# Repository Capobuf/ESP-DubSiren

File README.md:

# ESP32-S3 Dub Siren

Dub siren controllata da una GUI Windows. Il DSP gira interamente sull'ESP32-S3
e il PCM mono già elaborato può essere inviato al PC, a un DAC PCM5102A via
I2S, oppure a entrambe le destinazioni senza resampling.

La baseline predefinita **Classic** offre SINE 1, SINE 2, TEST TONE e
SQUARE, Pitch a tre posizioni e Rate a tre velocità più Manual. Il dry usa solo
un gate anti-click di 2 ms in attacco e 3 ms in rilascio. Echo Level zero esclude
completamente il wet. Le voci e la risposta dei controlli hanno una taratura
di progetto; una corrispondenza sonora con strumenti esterni non è misurata.

**Extended** conserva Lickshot, Sonar, Syndrum, Gunshot, Dynamic Sweep, forme
LFO aggiuntive e controlli avanzati, e aggiunge i carrier SAW e TRIANGLE.
Sine 1 e Sine 2 usano le stesse voci di
Classic; Sonar emette ping pulsanti con cadenza regolata da Rate.
Il DSP/control C++ è condiviso da firmware
e Virtual ESP. Tarature, fonti e limiti sono in [controls](docs/controls.md);
le verifiche della revisione sono in [baseline validation](docs/baseline-validation.md).

## Requisiti Windows

- ESP32-S3 DevKitC-1 collegata con un cavo USB dati
- modulo DAC PCM5102A per l'uscita audio GPIO
- display Adafruit 5393 / ST7789 opzionale per lo sviluppo firmware; il
  montaggio sul PCB resta da validare, come descritto sotto
- VS Code con estensione PlatformIO IDE, oppure PlatformIO Core 6.x
- Python 3.11 o successivo (verificato con Python 3.13.14)
- uscita audio Windows

La configurazione usa il profilo PlatformIO `esp32-s3-devkitc-1-n16r8`,
flash da 16 MB, Hardware CDC e USB Serial/JTAG. Il display non richiede PSRAM.

## Preparazione

Aprire un prompt nella cartella `pc` ed eseguire una volta:

```bat
setup.bat
```

Lo script crea `.venv`, aggiorna pip e installa `pyserial`, `sounddevice`
e il compilatore host `ziglang` per Virtual ESP.

## Build e upload firmware

Da un terminale nella cartella `firmware`:

```powershell
python -m platformio run
python -m platformio run --target upload --upload-port COM6
```

Sostituire `COM6` con la porta effettiva. Usare la connessione USB nativa che
Windows identifica come Espressif USB Serial/JTAG (`VID 303A`, `PID 1001`), non
una porta Bluetooth. Al primo upload può essere necessario entrare nel
bootloader: tenere premuto **BOOT**, premere e rilasciare **RESET/EN**, quindi
rilasciare **BOOT**. Dopo l'upload, se resta nel bootloader, premere una volta
solo **RESET/EN**.

In VS Code sono equivalenti i comandi **PlatformIO: Build** e
**PlatformIO: Upload**.

## Collegamento PCM5102A

Il DAC usa I2S Philips standard a 48 kHz, stereo 16 bit. Il firmware duplica
ogni campione mono sui canali sinistro e destro; il PCM5102A ricava internamente
il clock necessario e non richiede MCLK dall'ESP32.

```text
ESP32 GPIO16 -> PCM5102A BCK
ESP32 GPIO17 -> PCM5102A LCK
ESP32 GPIO18 -> PCM5102A DIN
PCM5102A SCL/SCK -> GND
PCM5102A FMT -> GND
```

## Avvio

Dalla cartella `pc`:

```bat
run.bat
```

La GUI funziona sia con l'ESP32-S3 reale sia senza hardware tramite **Virtual ESP**.
Il Virtual ESP compila e usa direttamente gli stessi sorgenti C++ DSP/control
del firmware; la libreria host viene ricompilata automaticamente quando quei
sorgenti cambiano.

La superficie predefinita presenta PITCH, RATE, ECHO LEVEL, ECHO TIME,
ECHO FEEDBACK ed ECHO FILTER; BTN1 TRIGGER, BTN2 HOLD, BTN3 MANUAL MOD e
BTN4 ECHO CUT. L'encoder cicla i quattro voicing; premendolo si apre il menu
al rilascio del click. I sei pot e i quattro pulsanti sono configurabili per
profilo dal controller C++ condiviso; Pickup evita salti dopo cambio profilo o
parametro. In Extended la rotazione libera cambia la variante del pad;
BTN1 premuto + rotazione regola Depth. Con gli altri pulsanti sonori
fisicamente premuti, l'encoder applica un transpose live temporaneo; in
Classic vale anche per BTN1. Il Master resta separato e non assegnabile sul
retro. La Home 320x172 mostra insieme etichette e valori fisici, con overlay
temporanei dei pot.
Il prodotto finale userà un display piccolo, principalmente testuale, per
stato, parametri, menu e impostazioni. Classic ed Extended mostrano solo testo;
il driver ST7789 usa la configurazione del 5393, ancora da verificare su hardware.
Dettagli: [pannello UI](docs/panel-ui.md).

Per lavorare senza hardware:

1. scegliere **Virtual ESP** nel selettore Device;
2. premere **Connect**;
3. premere **Start Audio**;
4. usare normalmente tutti i controlli della sirena.

In modalità Virtual ESP l'uscita è sempre **PC**. La catena fisica
I2S -> PCM5102A -> uscita analogica non è emulata.

Con l'hardware reale:

1. premere **Refresh** e scegliere la COM Espressif;
2. scegliere **PC**, **PCM5102A** o **Both** nel selettore Output;
3. premere **Connect** e attendere `Connected · firmware 0.9.0`;
4. premere **Start Audio**;
5. usare BTN1 Trigger, BTN2 Hold, BTN3 Manual Mod e BTN4 Echo Cut;
   ruotare l'encoder per scegliere il voicing, premerlo per il menu.

**Stop Audio** silenzia sia il PC sia il DAC. **Connect** prende il controllo
delle uscite e le mantiene silenziose fino a **Start Audio**; **Disconnect**
le silenzia e chiude audio, thread e seriale. Il DSP continua a elaborare le
code echo. Dopo Disconnect il DAC resta disabilitato fino a un nuovo Start,
`LOCAL_AUDIO 1` o riavvio; all'accensione l'uso autonomo resta abilitato.
Per un controllo automatico dell'hardware collegato:

```powershell
.venv\Scripts\python.exe smoke_test.py COM6
```

Dettagli: [architettura](docs/architecture.md), [protocollo](docs/protocol.md) e
[controlli](docs/controls.md).

Per creare ventotto brevi WAV di confronto direttamente dal PCM firmware
(con la scheda collegata), eseguire dalla cartella `pc`:

```powershell
.venv\Scripts\python.exe performance_capture.py COM6
```

Lo script stampa la directory temporanea che contiene i WAV. Usare
`--output-dir <percorso>` per scegliere una destinazione persistente. Il profilo
CLASSIC offre preset di progetto, non una riproduzione misurata di altri modelli.
Le capture includono Dynamic Sweep su SINE1/LICKSHOT/SONAR, Syndrum up/down e
sine/square, più Gunshot dry/echo; richiedono hardware reale e non costituiscono
uno smoke test I2S/DAC.

## Test

La [CI](.github/workflows/ci.yml) esegue i test Python/Virtual ESP e DSP nativi
su Windows e compila entrambi i firmware su Ubuntu. I binari e i file ELF
sono pubblicati come artefatti del run, separati per ambiente. Non viene
eseguito alcun upload su scheda. Le versioni firmware sono fissate in
`firmware/platformio.ini`; la CI usa PlatformIO 6.2.0.

```powershell
pc\.venv\Scripts\python.exe -m unittest discover -s pc -p "test_*.py" -f
pc\.venv\Scripts\python.exe tests\native\run.py
pc\.venv\Scripts\python.exe -m platformio run -d firmware -e esp32-s3-devkitc-1-n16r8 -e panel-prototype
```

Il test nativo usa Zig C++ (`pip install ziglang`) oppure il compilatore indicato
da `CXX`; esegue parser e DSP senza scheda. Con hardware collegato, leggere
`renderUs`, `maxRenderUs`, `cycleUs` e `maxCycleUs` da STATUS durante gli scenari
di sweep e verificare che restino sotto 10.000 µs per blocco.
`displayRenderUs` e `maxDisplayRenderUs` misurano separatamente il ridisegno
del testo ST7789 e devono restare sotto il budget display di 100.000 µs.

## Hardware

**PCB desktop a vista** 86 × 126 mm, senza custodia obbligatoria:
ESP32-S3-WROOM-1U, DAC Adafruit 6250 e display Adafruit 5393, solder mask nero
con finitura ENIG, quattro fissaggi M3. Il PCB è instradato e passa il DRC; il
montaggio fisico resta da provare sul prototipo.

- [Hardware: stato, decisioni e file](hardware/README.md)
- [Riferimento tecnico del PCB](hardware/docs/pcb.md), [guida di montaggio DIY](hardware/docs/assembly.md)

Il firmware configura il 5393 con `init(172, 320)` e rotazione landscape,
ottenendo un'area runtime di 320×172. Usa lo SPI hardware esistente:

```text
GPIO7  -> TFT RST
GPIO8  -> TFT DC
GPIO9  -> TFT CS
GPIO11 -> TFT MOSI
GPIO12 -> TFT SCK
GPIO14 -> backlight (livello fisso HIGH)
```

GPIO13/MISO non serve al TFT write-only e la microSD del breakout non è
implementata. Le librerie sono **Adafruit GFX Library** e **Adafruit ST7735 and
ST7789 Library**. In base alla [guida ufficiale Adafruit 5393](https://learn.adafruit.com/adafruit-1-47-round-rectangle-tft-display/arduino-wiring-test),
gli offset del pannello sono gestiti dalla libreria.

Il funzionamento del display sull'hardware reale e l'integrazione del firmware
con la scheda definitiva restano da verificare.

## Firmware per il pannello autonomo (issue #5-#12)

La revisione aggiunge articolazioni Lickshot, Tone/Contour, Echo Color,
menu Sound/Mod/Echo/Setup e quattro memorie Extended con SAVE/RECALL.
Vedi [controlli](docs/controls.md), [menu e memorie](docs/panel-ui.md) e
[pinout, build autonoma e verifiche hardware pendenti](docs/standalone.md).
`STREAM 0` interrompe soltanto USB; `LOCAL_AUDIO 0` silenzia l'uscita locale.
Le nuove tarature sonore richiedono ascolto e misure sull'ESP.

Il [tap tempo](docs/tempo.md) aggiunge BPM e divisioni ritmiche indipendenti
per Echo e LFO, con azione pulsante assegnabile e accesso dal menu.

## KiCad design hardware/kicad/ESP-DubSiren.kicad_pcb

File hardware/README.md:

# ESP-DubSiren — hardware

PCB desktop a vista, unico progetto KiCad attivo. Instradato, con DRC a 0 errori
(18 esclusioni volute per lo stack U5/U6), 0 connessioni aperte e schema allineato.
Gerber e forature per JLCPCB generati l'8/11/2026 in [fab/](fab/), non ancora ordinati.

## File

| Cosa | Dove |
|---|---|
| Progetto, schema, PCB | [kicad/ESP-DubSiren.kicad_pro](kicad/ESP-DubSiren.kicad_pro), [schema](kicad/ESP-DubSiren.kicad_sch), [PCB](kicad/ESP-DubSiren.kicad_pcb) |
| Librerie locali | [footprint](kicad/footprints/), [simboli](kicad/symbols/) |
| Riferimento tecnico del PCB | [docs/pcb.md](docs/pcb.md) |
| Gerber e forature JLCPCB | [fab/ESP-DubSiren-JLCPCB-2026-11-08.zip](fab/ESP-DubSiren-JLCPCB-2026-11-08.zip), file singoli e mappe fori in [fab/ESP-DubSiren-JLCPCB-2026-11-08/](fab/ESP-DubSiren-JLCPCB-2026-11-08/) |
| Montaggio DIY | [docs/assembly.md](docs/assembly.md) |
| Distinta e acquisti | [docs/BOM.csv](docs/BOM.csv), [docs/acquisti.csv](docs/acquisti.csv) |
| Datasheet e disegni | [docs/sources.md](docs/sources.md), [cad/sources/](cad/sources/) |
| Modelli 3D | [cad/3dmodels/](cad/3dmodels/README.md), generati e assegnati con [tools/](tools/) |

## Decisioni in vigore

- **Scheda:** 86 × 126 mm, angoli R3, 2 strati, 1,6 mm. Nessuna custodia, staffa
  USB o stampa 3D obbligatoria; si usa orizzontale o leggermente inclinata.
- **Produzione:** JLCPCB, solder mask nero, finitura ENIG 1µ", serigrafia bianca.
  Sono già impostati nello stackup del PCB; vanno selezionati anche nell'ordine.
- **Fissaggi:** quattro fori M3 Ø3,2 NPTH in (5;−1), (81;−1), (5;115), (81;115),
  interassi 76 × 116 mm, con riserve 8 × 8 mm senza rame su entrambe le facce.
  Origine KiCad: bordo posteriore Y=−6, anteriore Y=120.
- **Fronte (F.Cu):** RV1–3 in alto, display U5 (Adafruit 5393) al centro con
  encoder SW7 a destra, RV4–6 sotto, quattro CHERRY SW1–4 in basso.
- **Bordo posteriore:** USB-C J1 (GCT USB4085), jack mono J2 (Neutrik NRJ4HF),
  MASTER RV7. RESET SW5 e BOOT SW6 sul bordo destro.
- **Retro (B.Cu):** tutti gli SMD; ESP32-S3-WROOM-1U-N16R8 (U1) a sinistra.
  Il DAC U6 (Adafruit 6250, senza jack 3,5 mm) sta dietro il display U5:
  header U5 da 2,50 mm, pin U6 tagliati a filo prima di montare U5. Eventuali
  adattamenti (pin più alti o simili) si fanno a mano in montaggio.
- **Uscita audio J2:** T → AUDIO_MONO (OUTL di U6), S → GND, TN/SN non collegati;
  OUTR di U6 non collegato. Il dado NRJ-NUT-B serve solo con un pannello.
- **Archivio Hammond:** lo studio della issue
  [#14](https://github.com/Capobuf/ESP-DubSiren/issues/14) è conservato nel branch
  `codex/issue-14-jack-fit`. Non va eliminato e non vincola il layout.

## Da verificare sul prototipo

- Stack U5/U6: altezza reale fra display e DAC.
- Fit di manopole, keycap e distanziali; stabilità degli appoggi.
- Ripple delle alimentazioni, rumore audio, I²S e display sull'hardware reale.

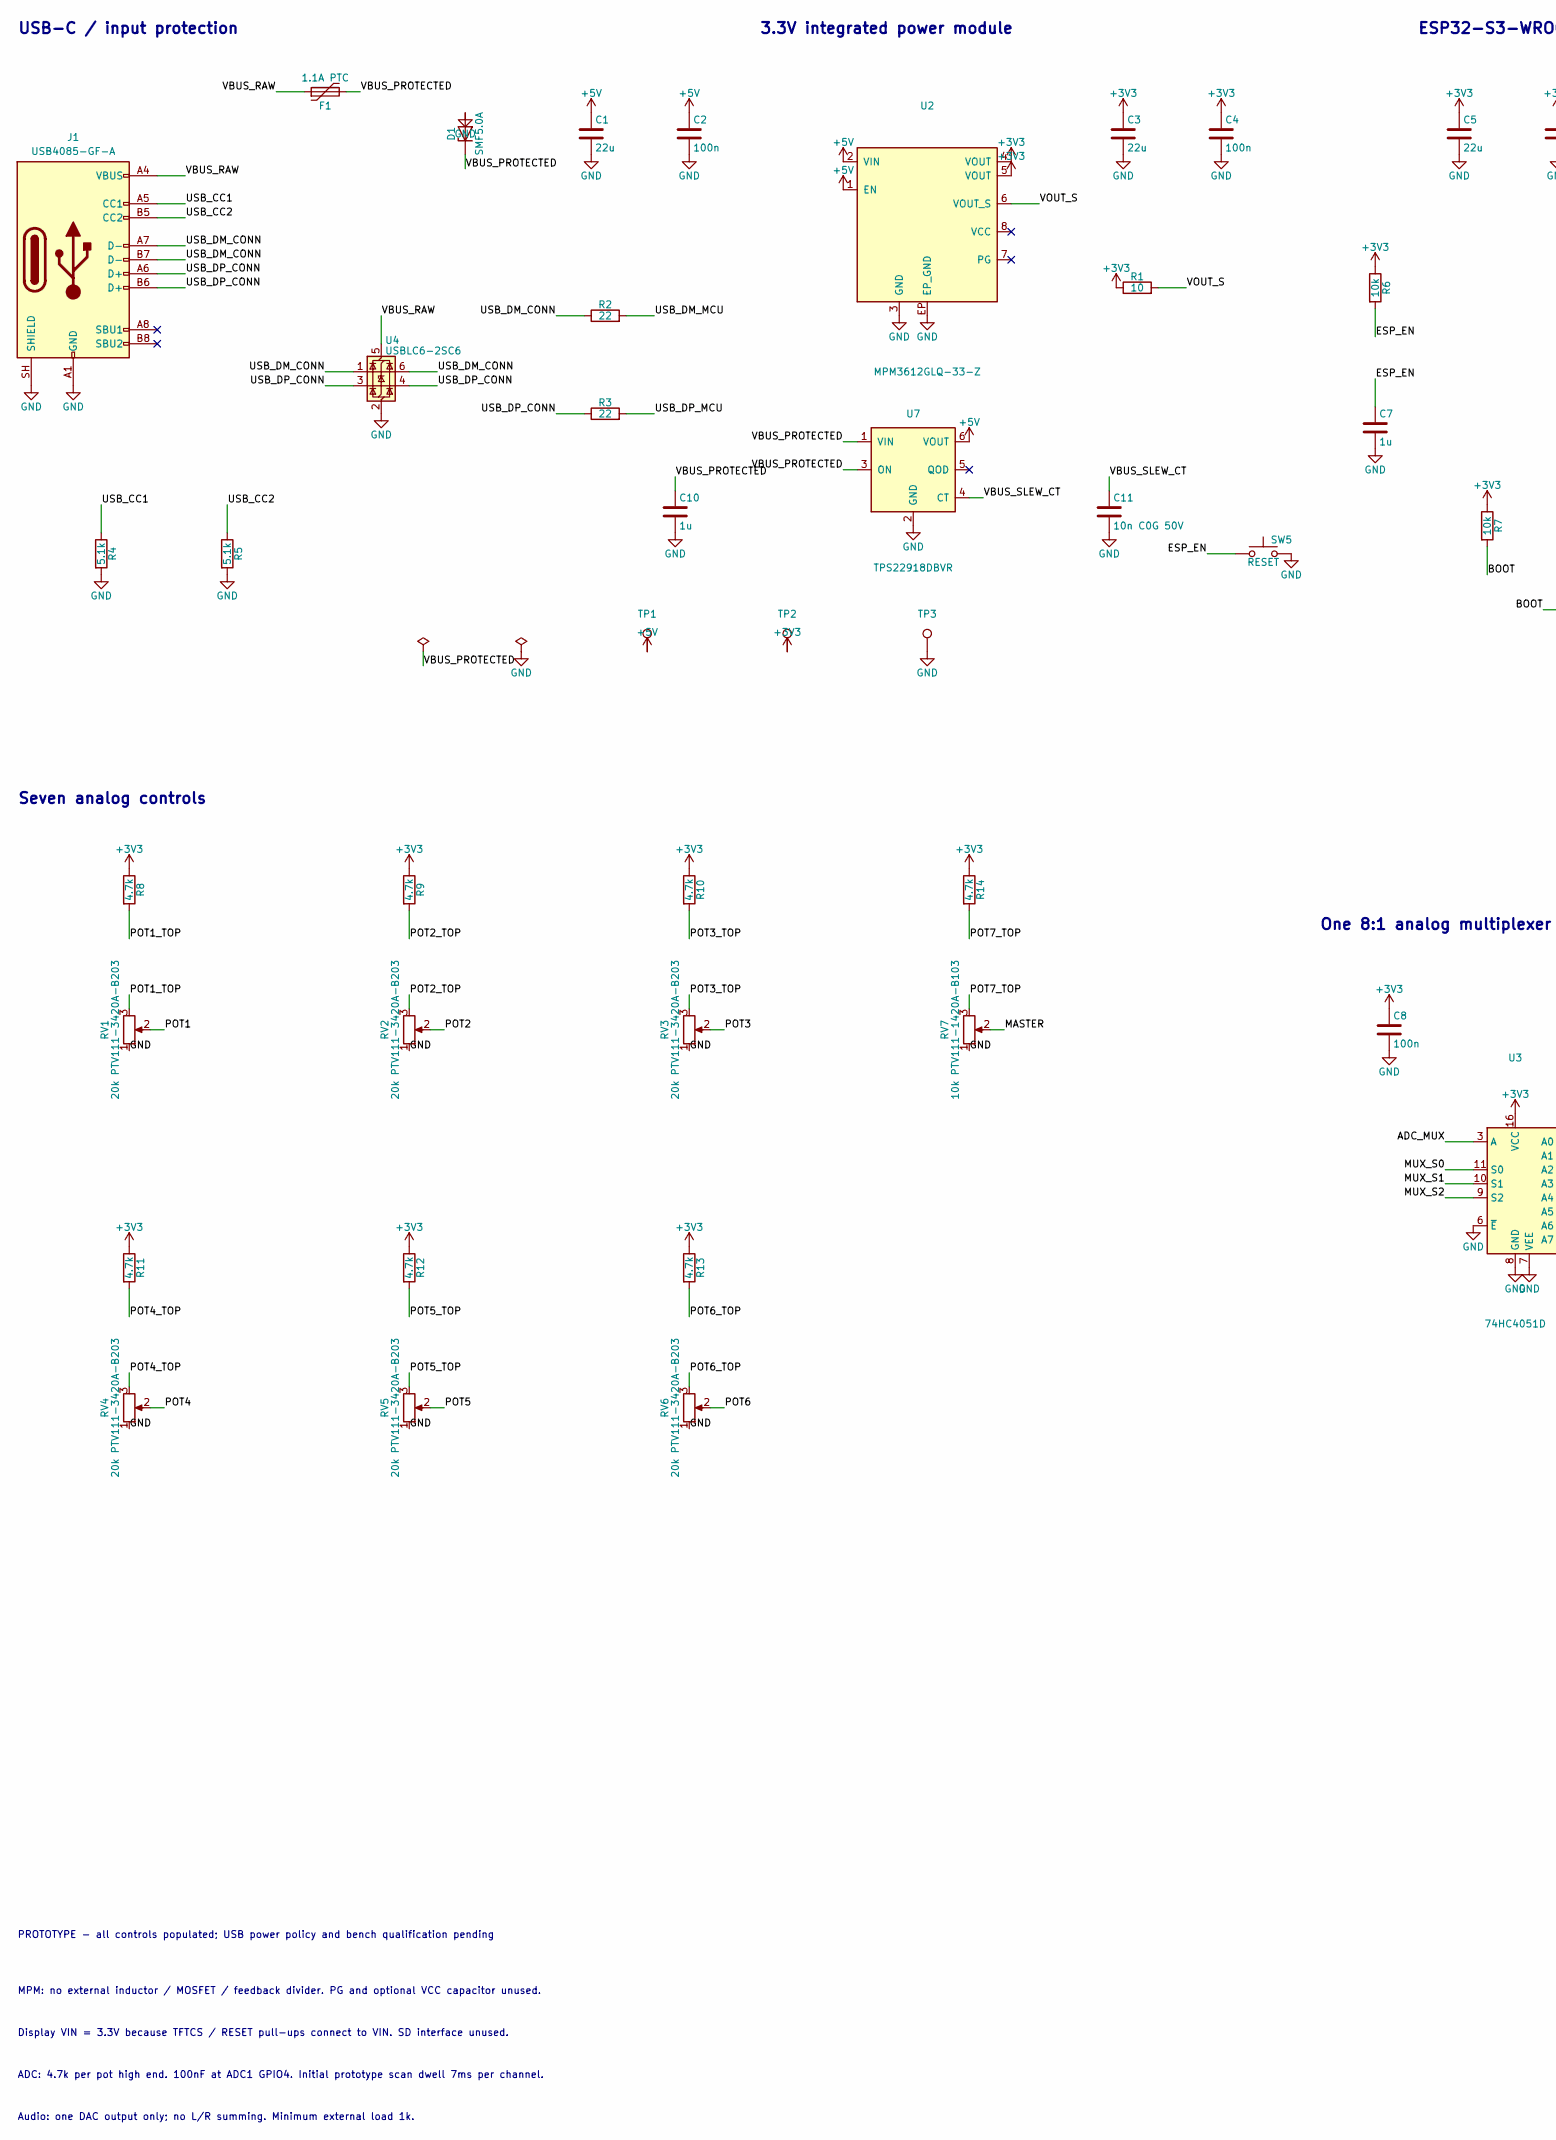
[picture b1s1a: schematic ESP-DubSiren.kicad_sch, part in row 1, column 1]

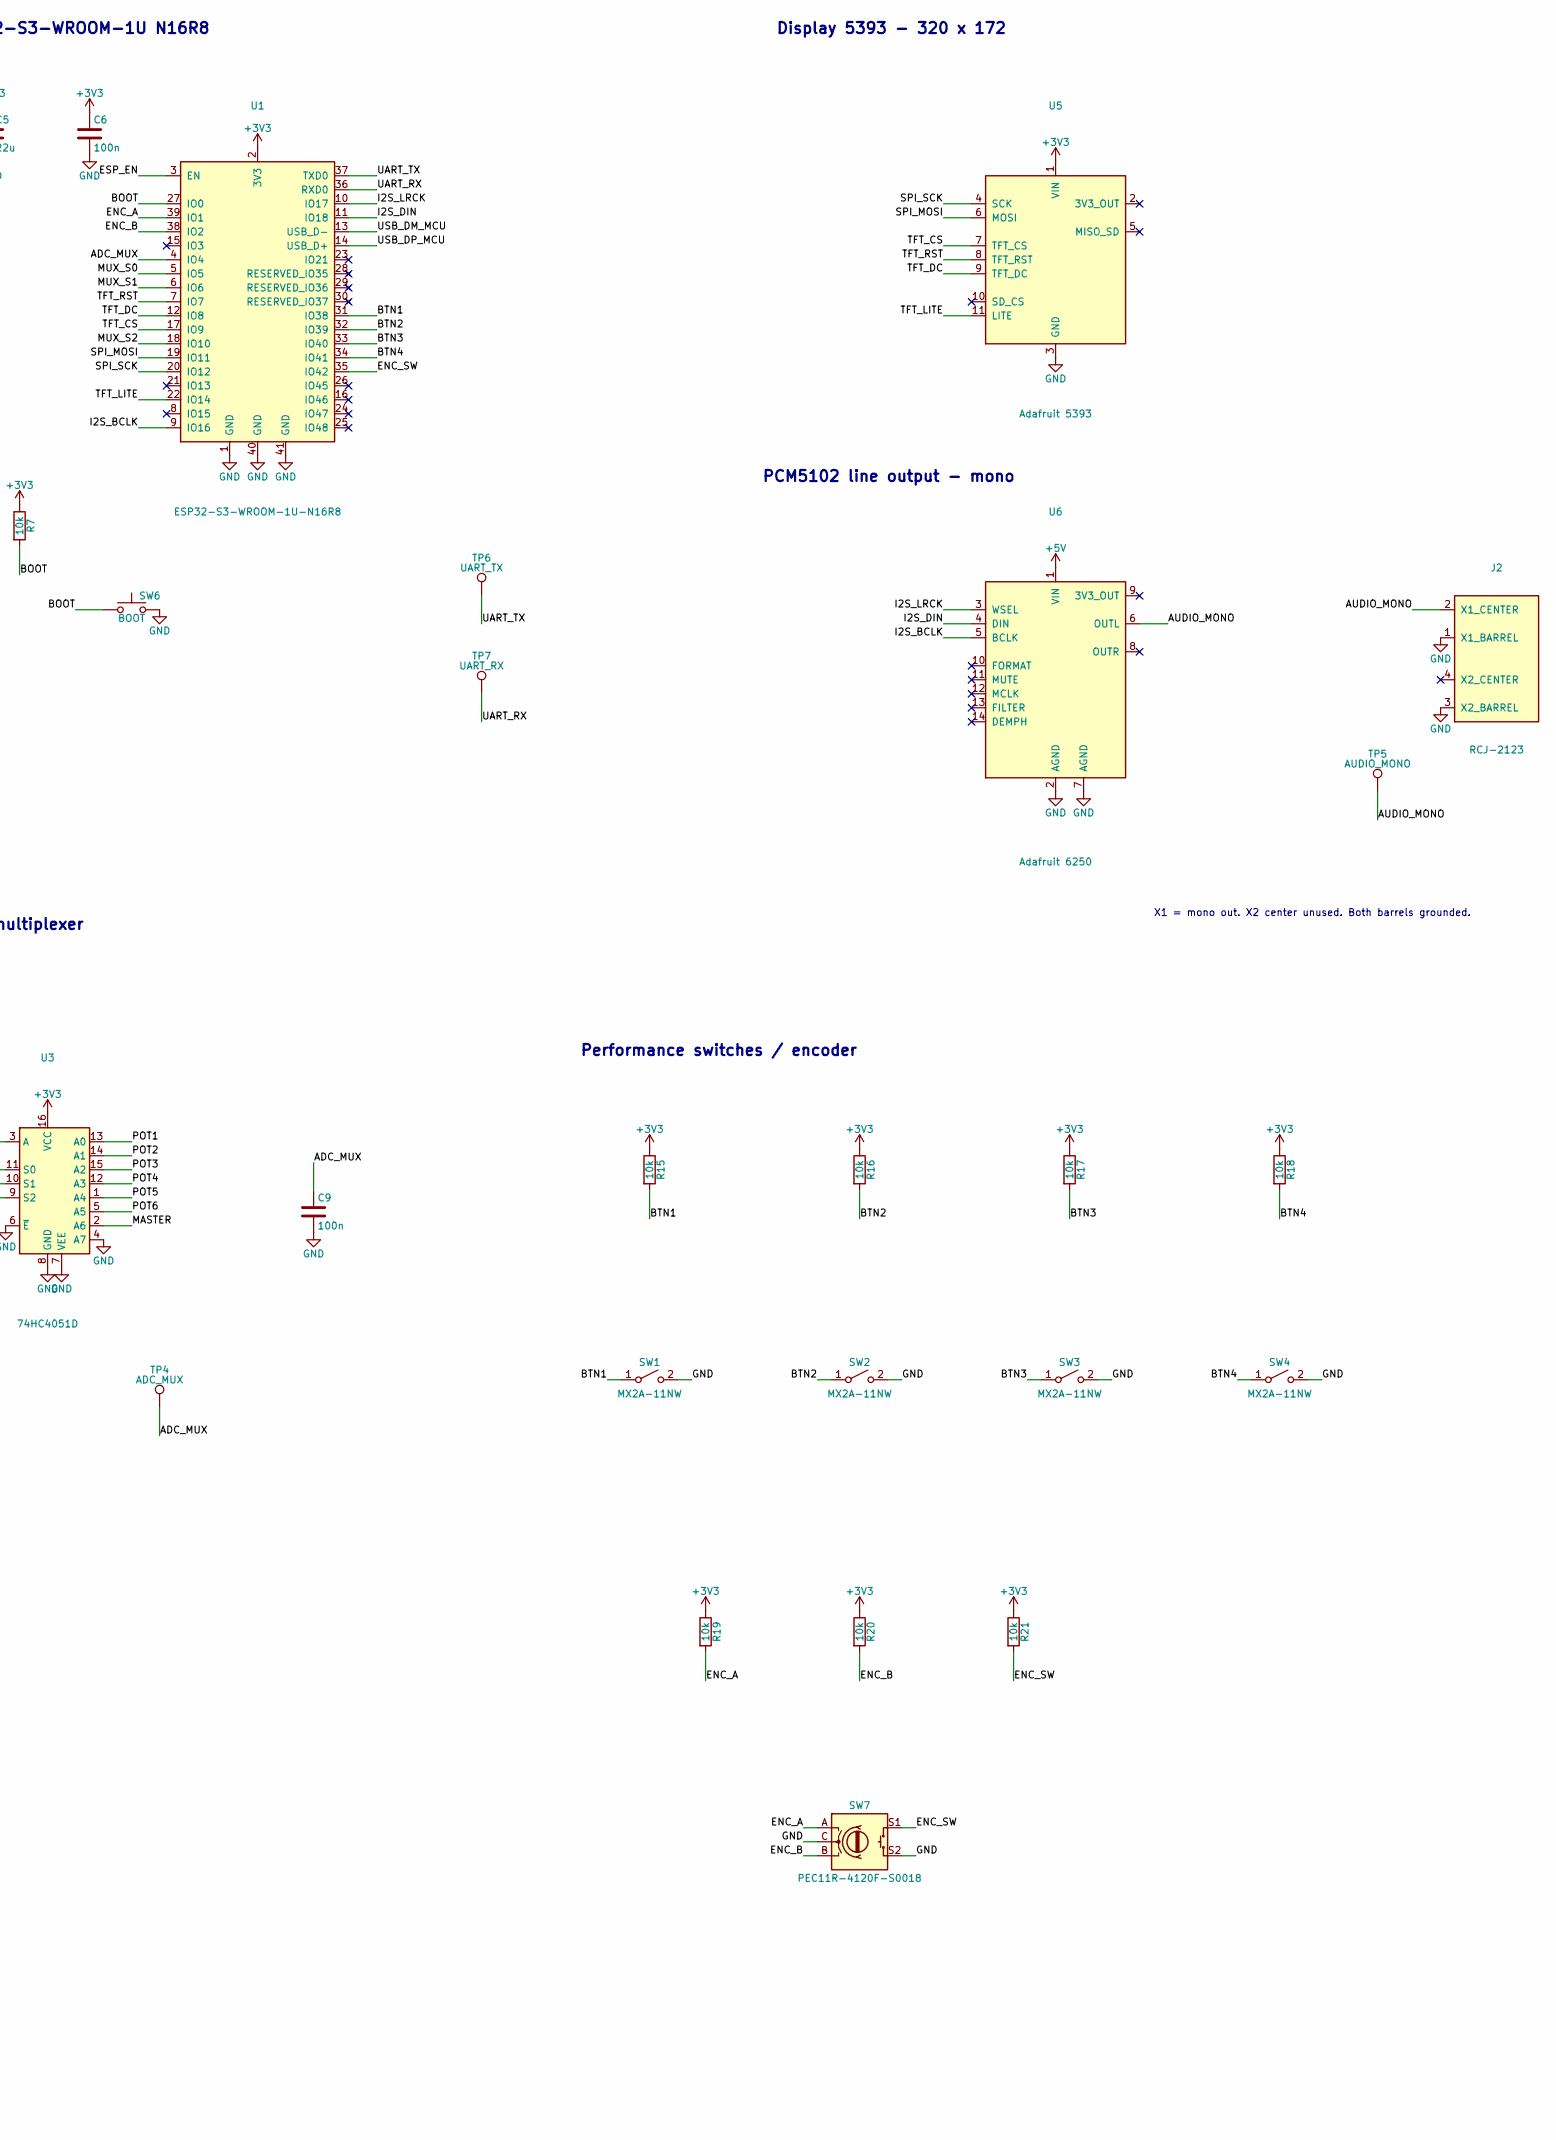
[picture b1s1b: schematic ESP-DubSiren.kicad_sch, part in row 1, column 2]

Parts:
C1, C3, C5: 22u; C_0805_2012Metric; MPN CL21A226MPCLRNC
C2, C4, C6, C8, C9: 100n; C_0603_1608Metric; MPN CL10B104KO8NNNC
C7, C10: 1u; C_0603_1608Metric; MPN CL10B105MO8NNWC
C11: 10n C0G 50V; C_0603_1608Metric; MPN GRM1885C1H103JA01D
D1: SMF5.0A; D_SOD-123F; MPN SMF5.0A_R1_00001
F1: 1.1A PTC; Bel_0ZCG0110CF2B_1812; MPN 0ZCG0110CF2B
J1: USB4085-GF-A; USB_C_Receptacle_GCT_USB4085; MPN USB4085-GF-A
J2: RCJ-2123; SameSky_RCJ-2123; MPN RCJ-2123
R1: 10; R_0603_1608Metric; MPN NRC06J100TRF
R2, R3: 22; R_0603_1608Metric; MPN RC0603JR-0722RL
R4, R5: 5.1k; R_0603_1608Metric; MPN AC0603FR-075K1L
R6, R7, R15, R16, R17, R18, R19, R20, R21: 10k; R_0603_1608Metric; MPN RC0603JR-0710KL
R8, R9, R10, R11, R12, R13, R14: 4.7k; R_0603_1608Metric; MPN RC0603FR-074K7L
RV1, RV2, RV3, RV4, RV5, RV6: 20k PTV111-3420A-B203; Bourns_PTV111-3; MPN PTV111-3420A-B203
RV7: 10k PTV111-1420A-B103; Bourns_PTV111-1; MPN PTV111-1420A-B103
SW1, SW2, SW3, SW4: MX2A-11NW; SW_Cherry_MX_1.00u_PCB; MPN MX2A-11NW
SW5: RESET; CK_PTS636SM43SMTR_LFS; MPN PTS636SM43SMTR LFS
SW6: BOOT; CK_PTS636SM43SMTR_LFS; MPN PTS636SM43SMTR LFS
SW7: PEC11R-4120F-S0018; Bourns_PEC11R-4120F-S0018; MPN PEC11R-4120F-S0018
TP1: +5V; TestPoint_Pad_D1.0mm; MPN PCB test pad
TP2: +3V3; TestPoint_Pad_D1.0mm; MPN PCB test pad
TP3: GND; TestPoint_Pad_D1.0mm; MPN PCB test pad
TP4: ADC_MUX; TestPoint_Pad_D1.0mm; MPN PCB test pad
TP5: AUDIO_MONO; TestPoint_Pad_D1.0mm; MPN PCB test pad
TP6: UART_TX; TestPoint_Pad_D1.0mm; MPN PCB test pad
TP7: UART_RX; TestPoint_Pad_D1.0mm; MPN PCB test pad
U1: ESP32-S3-WROOM-1U-N16R8; Espressif_ESP32-S3-WROOM-1U; MPN ESP32-S3-WROOM-1U-N16R8
U2: MPM3612GLQ-33-Z; MPS_MPM3612GLQ-33_LGA-8-1EP_3x3mm; MPN MPM3612GLQ-33-Z
U3: 74HC4051D; SOIC-16_3.9x9.9mm_P1.27mm; MPN 74HC4051D
U4: USBLC6-2SC6; SOT-23-6; MPN USBLC6-2SC6
U5: Adafruit 5393; Adafruit_5393_DisplayFace; MPN 5393
U6: Adafruit 6250; Adafruit_6250_ComponentFace; MPN 6250
U7: TPS22918DBVR; SOT-23-6; MPN TPS22918DBVR

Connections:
+3V3: C3.1, C4.1, C5.1, C6.1, C8.1, R1.1, R6.1, R7.1, R8.1, R9.1, R10.1, R11.1, R12.1, R13.1, R14.1, R15.1, R16.1, R17.1, R18.1, R19.1, R20.1, R21.1, TP2.1 (1_1), U1.2 (3V3), U2.4 (VOUT), U2.5 (VOUT), U3.16 (VCC), U5.1 (VIN)
+5V: C1.1, C2.1, TP1.1 (1_1), U2.1 (EN), U2.2 (VIN), U6.1 (VIN), U7.6 (VOUT)
/ADC_MUX: C9.1, TP4.1 (1_1), U1.4 (IO4), U3.3 (A)
/AUDIO_MONO: J2.2 (X1_CENTER), J2.T, TP5.1 (1_1), U6.6 (OUTL)
/BOOT: R7.2, SW6.1, U1.27 (IO0)
/BTN1: R15.2, SW1.1 (A), U1.31 (IO38)
/BTN2: R16.2, SW2.1 (A), U1.32 (IO39)
/BTN3: R17.2, SW3.1 (A), U1.33 (IO40)
/BTN4: R18.2, SW4.1 (A), U1.34 (IO41)
/ENC_A: R19.2, SW7.A, U1.39 (IO1)
/ENC_B: R20.2, SW7.B, U1.38 (IO2)
/ENC_SW: R21.2, SW7.S1, U1.35 (IO42)
/ESP_EN: C7.1, R6.2, SW5.1, U1.3 (EN)
/I2S_BCLK: U1.9 (IO16), U6.5 (BCLK)
/I2S_DIN: U1.11 (IO18), U6.4 (DIN)
/I2S_LRCK: U1.10 (IO17), U6.3 (WSEL)
/MASTER: RV7.2, U3.2 (A6)
/MUX_S0: U1.5 (IO5), U3.11 (S0)
/MUX_S1: U1.6 (IO6), U3.10 (S1)
/MUX_S2: U1.18 (IO10), U3.9 (S2)
/POT1: RV1.2, U3.13 (A0)
/POT1_TOP: R8.2, RV1.3
/POT2: RV2.2, U3.14 (A1)
/POT2_TOP: R9.2, RV2.3
/POT3: RV3.2, U3.15 (A2)
/POT3_TOP: R10.2, RV3.3
/POT4: RV4.2, U3.12 (A3)
/POT4_TOP: R11.2, RV4.3
/POT5: RV5.2, U3.1 (A4)
/POT5_TOP: R12.2, RV5.3
/POT6: RV6.2, U3.5 (A5)
/POT6_TOP: R13.2, RV6.3
/POT7_TOP: R14.2, RV7.3
/SPI_MOSI: U1.19 (IO11), U5.6 (MOSI)
/SPI_SCK: U1.20 (IO12), U5.4 (SCK)
/TFT_CS: U1.17 (IO9), U5.7 (TFT_CS)
/TFT_DC: U1.12 (IO8), U5.9 (TFT_DC)
/TFT_LITE: U1.22 (IO14), U5.11 (LITE)
/TFT_RST: U1.7 (IO7), U5.8 (TFT_RST)
/UART_RX: TP7.1 (1_1), U1.36 (RXD0)
/UART_TX: TP6.1 (1_1), U1.37 (TXD0)
/USB_CC1: J1.A5 (CC1), R4.1
/USB_CC2: J1.B5 (CC2), R5.1
/USB_DM_CONN: J1.A7 (D-), J1.B7 (D-), R2.1, U4.1 (I/O1), U4.6 (I/O1)
/USB_DM_MCU: R2.2, U1.13 (USB_D-)
/USB_DP_CONN: J1.A6 (D+), J1.B6 (D+), R3.1, U4.3 (I/O2), U4.4 (I/O2)
/USB_DP_MCU: R3.2, U1.14 (USB_D+)
/VBUS_PROTECTED: C10.1, D1.1 (K), F1.2, U7.1 (VIN), U7.3 (ON)
/VBUS_RAW: F1.1, J1.A4 (VBUS), J1.A9 (VBUS), J1.B4 (VBUS), J1.B9 (VBUS), U4.5 (VBUS)
/VBUS_SLEW_CT: C11.1, U7.4 (CT)
/VOUT_S: R1.2, U2.6 (VOUT_S)
GND: C1.2, C2.2, C3.2, C4.2, C5.2, C6.2, C7.2, C8.2, C9.2, C10.2, C11.2, D1.2 (A), J1.A1 (GND), J1.A12 (GND), J1.B1 (GND), J1.B12 (GND), J1.SH (SHIELD), J2.1 (X1_BARREL), J2.3 (X2_BARREL), J2.S, R4.2, R5.2, RV1.1, RV2.1, RV3.1, RV4.1, RV5.1, RV6.1, RV7.1, SW1.2 (B), SW2.2 (B), SW3.2 (B), SW4.2 (B), SW5.2, SW6.2, SW7.C, SW7.S2, TP3.1 (1_1), U1.1 (GND), U1.40 (GND), U1.41 (GND), U2.3 (GND), U2.EP (EP_GND), U3.4 (A7), U3.6 (~E), U3.7 (VEE), U3.8 (GND), U4.2 (GND), U5.3 (GND), U6.2 (AGND), U6.7 (AGND), U7.2 (GND)

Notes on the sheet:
USB-C / input protection
3.3V integrated power module
ESP32-S3-WROOM-1U N16R8
Display 5393 - 320 x 172
PCM5102 line output - mono
Seven analog controls
One 8:1 analog multiplexer
Performance switches / encoder
MPM: no external inductor / MOSFET / feedback divider. PG and optional VCC capacitor unused.
Display VIN = 3.3V because TFTCS / RESET pull-ups connect to VIN. SD interface unused.
ADC: 4.7k per pot high end. 100nF at ADC1 GPIO4. Initial prototype scan dwell 7ms per channel.
Audio: one DAC output only; no L/R summing. Minimum external load 1k.
X1 = mono out. X2 center unused. Both barrels grounded.
PROTOTYPE - all controls populated; USB power policy and bench qualification pending

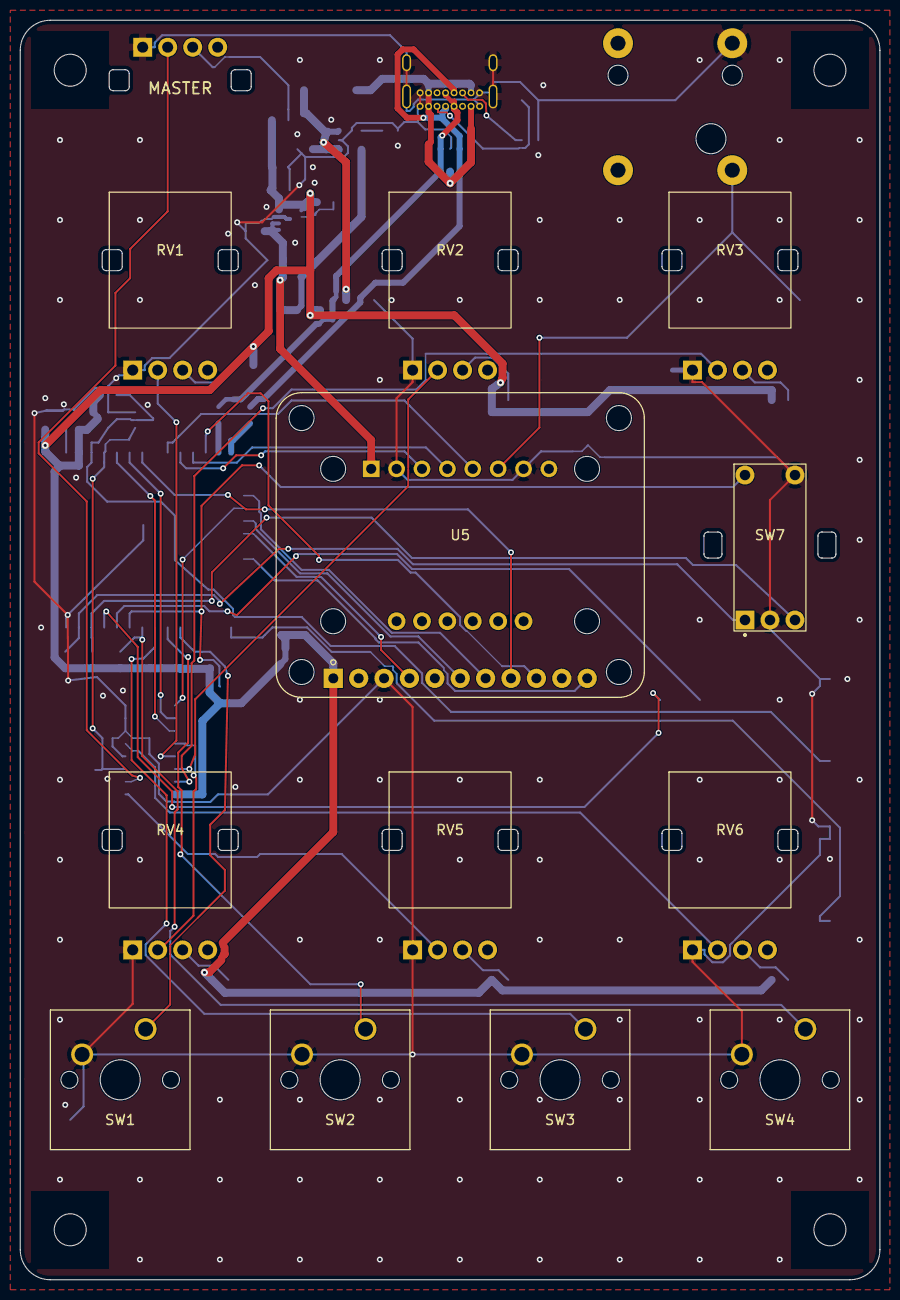
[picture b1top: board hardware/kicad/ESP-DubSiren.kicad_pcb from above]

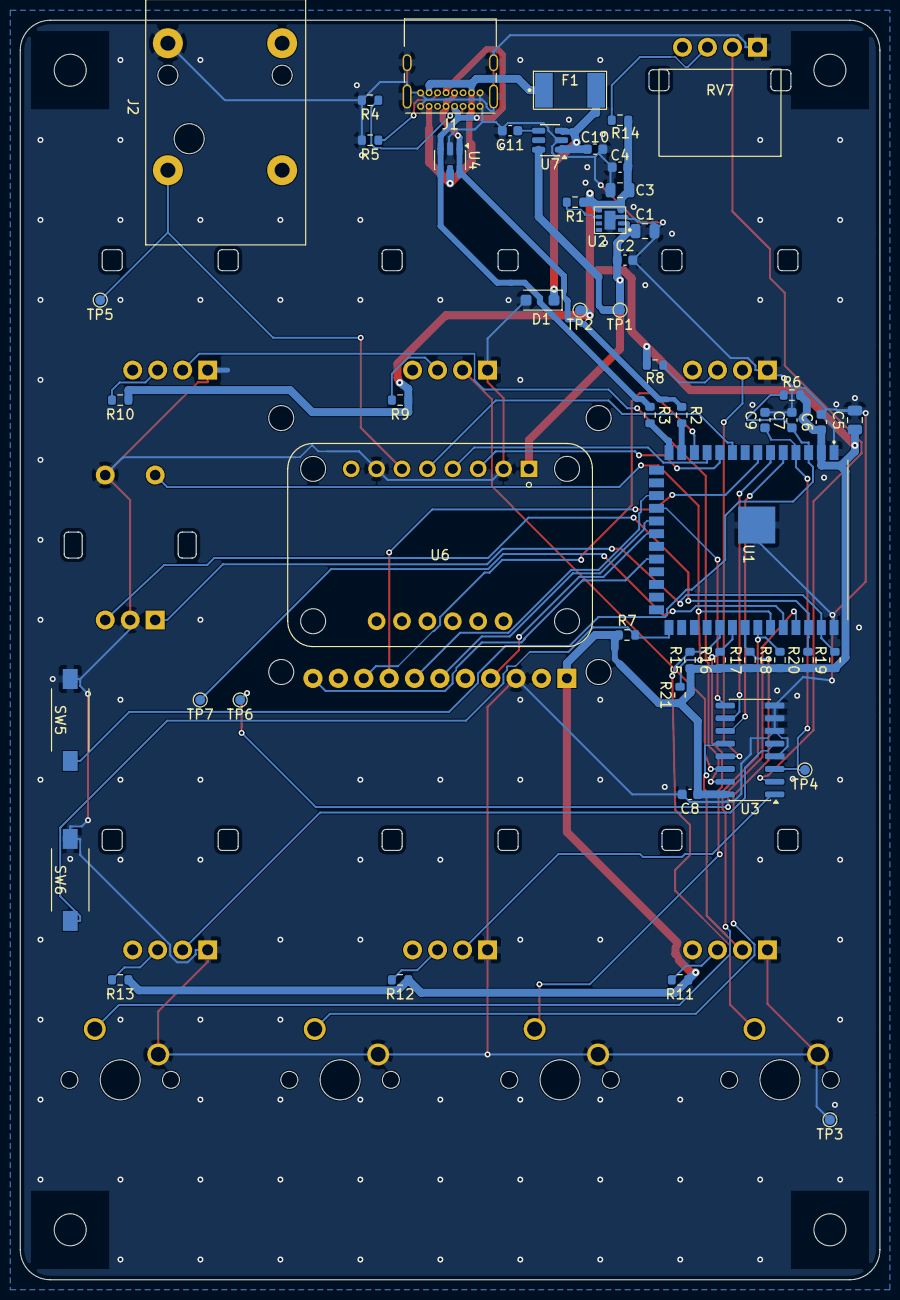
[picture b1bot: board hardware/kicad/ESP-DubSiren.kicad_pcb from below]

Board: 2 copper layers, 86.0 x 126.0 mm, 68 parts (52 on the bottom side), 52 nets.

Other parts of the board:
H1, H2, H3, H4: MountingHole_3.2mm_M3

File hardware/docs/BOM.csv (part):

Reference,Value,Quantity,Footprint,MPN,Manufacturer,Datasheet,DNP,Purchasable,Notes
C1,22u,1,Capacitor_SMD:C_0805_2012Metric,CL21A226MPCLRNC,Samsung,,,yes,Componente dello schema provvisorio; validazione hardware pendente
C2,100n,1,Capacitor_SMD:C_0603_1608Metric,CL10B104KO8NNNC,Samsung,,,yes,Componente dello schema provvisorio; validazione hardware pendente
C3,22u,1,Capacitor_SMD:C_0805_2012Metric,CL21A226MPCLRNC,Samsung,,,yes,Componente dello schema provvisorio; validazione hardware pendente
C4,100n,1,Capacitor_SMD:C_0603_1608Metric,CL10B104KO8NNNC,Samsung,,,yes,Componente dello schema provvisorio; validazione hardware pendente
C5,22u,1,Capacitor_SMD:C_0805_2012Metric,CL21A226MPCLRNC,Samsung,,,yes,Componente dello schema provvisorio; validazione hardware pendente
C6,100n,1,Capacitor_SMD:C_0603_1608Metric,CL10B104KO8NNNC,Samsung,,,yes,Componente dello schema provvisorio; validazione hardware pendente
C7,1u,1,Capacitor_SMD:C_0603_1608Metric,CL10B105MO8NNWC,Samsung,,,yes,Componente dello schema provvisorio; validazione hardware pendente
C8,100n,1,Capacitor_SMD:C_0603_1608Metric,CL10B104KO8NNNC,Samsung,,,yes,Componente dello schema provvisorio; validazione hardware pendente
C9,100n,1,Capacitor_SMD:C_0603_1608Metric,CL10B104KO8NNNC,Samsung,,,yes,Componente dello schema provvisorio; validazione hardware pendente
C10,1u,1,Capacitor_SMD:C_0603_1608Metric,CL10B105MO8NNWC,Samsung,https://product.samsungsem.com/mlcc/CL10B105MO8NNW.do,,yes,Componente dello schema provvisorio; validazione hardware pendente
C11,10n C0G 50V,1,Capacitor_SMD:C_0603_1608Metric,GRM1885C1H103JA01D,Murata,https://search.murata.co.jp/Ceramy/image/img/A01X/G101/ENG/G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,,yes,Componente dello schema provvisorio; validazione hardware pendente
D1,SMF5.0A,1,Diode_SMD:D_SOD-123F,SMF5.0A_R1_00001,PANJIT,https://www.panjit.com.cn/upload/datasheet/SMF5.0A_SERIES.pdf,,yes,Componente dello schema provvisorio; validazione hardware pendente
F1,1.1A PTC,1,ESP-DubSiren-V2-Electrical:Bel_0ZCG0110CF2B_1812,0ZCG0110CF2B,Bel,https://www.belfuse.com/resources/datasheets/circuitprotecti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,,yes,Componente dello schema provvisorio; validazione hardware pendente
J1,USB4085-GF-A,1,Connector_USB:USB_C_Receptacle_GCT_USB4085,USB4085-GF-A,GCT,https://az.y-ic.com/datasheet/e9/USB4085-GF-A.pdf,,yes,Componente dello schema provvisorio; validazione hardware pendente
J2,NRJ4HF,1,Connector_Audio:Jack_6.35mm_Neutrik_NRJ4HF_Horizontal,NRJ4HF,Neutrik,https://www.neutrik.com/media/8561/download/st-nrj4hf.PDF?v=2,,yes,Mono TS: T=AUDIO_MONO OUTL; S=GND; TN/SN NC; dado NRJ-NUT-B x1 facoltativo senza pannello; proposta standalone da validare
R1,10,1,Resistor_SMD:R_0603_1608Metric,NRC06J100TRF,NIC,,,yes,Componente dello schema provvisorio; validazione hardware pendente
R2,22,1,Resistor_SMD:R_0603_1608Metric,RC0603JR-0722RL,Yageo,,,yes,Componente dello schema provvisorio; validazione hardware pendente
R3,22,1,Resistor_SMD:R_0603_1608Metric,RC0603JR-0722RL,Yageo,,,yes,Componente dello schema provvisorio; validazione hardware pendente
R4,5.1k,1,Resistor_SMD:R_0603_1608Metric,AC0603FR-075K1L,Yageo,,,yes,Componente dello schema provvisorio; validazione hardware pendente
R5,5.1k,1,Resistor_SMD:R_0603_1608Metric,AC0603FR-075K1L,Yageo,,,yes,Componente dello schema provvisorio; validazione hardware pendente
R6,10k,1,Resistor_SMD:R_0603_1608Metric,RC0603JR-0710KL,Yageo,,,yes,Componente dello schema provvisorio; validazione hardware pendente
R7,10k,1,Resistor_SMD:R_0603_1608Metric,RC0603JR-0710KL,Yageo,,,yes,Componente dello schema provvisorio; validazione hardware pendente
R8,4.7k,1,Resistor_SMD:R_0603_1608Metric,RC0603FR-074K7L,Yageo,,,yes,Componente dello schema provvisorio; validazione hardware pendente
R9,4.7k,1,Resistor_SMD:R_0603_1608Metric,RC0603FR-074K7L,Yageo,,,yes,Componente dello schema provvisorio; validazione hardware pendente
R10,4.7k,1,Resistor_SMD:R_0603_1608Metric,RC0603FR-074K7L,Yageo,,,yes,Componente dello schema provvisorio; validazione hardware pendente
R11,4.7k,1,Resistor_SMD:R_0603_1608Metric,RC0603FR-074K7L,Yageo,,,yes,Componente dello schema provvisorio; validazione hardware pendente
R12,4.7k,1,Resistor_SMD:R_0603_1608Metric,RC0603FR-074K7L,Yageo,,,yes,Componente dello schema provvisorio; validazione hardware pendente
R13,4.7k,1,Resistor_SMD:R_0603_1608Metric,RC0603FR-074K7L,Yageo,,,yes,Componente dello schema provvisorio; validazione hardware pendente
R14,4.7k,1,Resistor_SMD:R_0603_1608Metric,RC0603FR-074K7L,Yageo,,,yes,Componente dello schema provvisorio; validazione hardware pendente
R15,10k,1,Resistor_SMD:R_0603_1608Metric,RC0603JR-0710KL,Yageo,,,yes,Componente dello schema provvisorio; validazione hardware pendente
R16,10k,1,Resistor_SMD:R_0603_1608Metric,RC0603JR-0710KL,Yageo,,,yes,Componente dello schema provvisorio; validazione hardware pendente
R17,10k,1,Resistor_SMD:R_0603_1608Metric,RC0603JR-0710KL,Yageo,,,yes,Componente dello schema provvisorio; validazione hardware pendente
R18,10k,1,Resistor_SMD:R_0603_1608Metric,RC0603JR-0710KL,Yageo,,,yes,Componente dello schema provvisorio; validazione hardware pendente
R19,10k,1,Resistor_SMD:R_0603_1608Metric,RC0603JR-0710KL,Yageo,,,yes,Componente dello schema provvisorio; validazione hardware pendente
R20,10k,1,Resistor_SMD:R_0603_1608Metric,RC0603JR-0710KL,Yageo,,,yes,Componente dello schema provvisorio; validazione hardware pendente
R21,10k,1,Resistor_SMD:R_0603_1608Metric,RC0603JR-0710KL,Yageo,,,yes,Componente dello schema provvisorio; validazione hardware pendente
RV1,20k PTV111-3420A-B203,1,ESP-DubSiren-V2-Mechanical:Bourns_PTV111-3,PTV111-3420A-B203,Bourns,https://bourns.com/docs/product-datasheets/ptvptt.pdf,,yes,Componente dello schema provvisorio; validazione hardware pendente
RV2,20k PTV111-3420A-B203,1,ESP-DubSiren-V2-Mechanical:Bourns_PTV111-3,PTV111-3420A-B203,Bourns,https://bourns.com/docs/product-datasheets/ptvptt.pdf,,yes,Componente dello schema provvisorio; validazione hardware pendente
RV3,20k PTV111-3420A-B203,1,ESP-DubSiren-V2-Mechanical:Bourns_PTV111-3,PTV111-3420A-B203,Bourns,https://bourns.com/docs/product-datasheets/ptvptt.pdf,,yes,Componente dello schema provvisorio; validazione hardware pendente
RV4,20k PTV111-3420A-B203,1,ESP-DubSiren-V2-Mechanical:Bourns_PTV111-3,PTV111-3420A-B203,Bourns,https://bourns.com/docs/product-datasheets/ptvptt.pdf,,yes,Componente dello schema provvisorio; validazione hardware pendente
RV5,20k PTV111-3420A-B203,1,ESP-DubSiren-V2-Mechanical:Bourns_PTV111-3,PTV111-3420A-B203,Bourns,https://bourns.com/docs/product-datasheets/ptvptt.pdf,,yes,Componente dello schema provvisorio; validazione hardware pendente
RV6,20k PTV111-3420A-B203,1,ESP-DubSiren-V2-Mechanical:Bourns_PTV111-3,PTV111-3420A-B203,Bourns,https://bourns.com/docs/product-datasheets/ptvptt.pdf,,yes,Componente dello schema provvisorio; validazione hardware pendente
RV7,10k PTV111-1420A-B103,1,ESP-DubSiren-V2-Mechanical:Bourns_PTV111-1,PTV111-1420A-B103,Bourns,https://bourns.com/docs/product-datasheets/ptvptt.pdf,,yes,Componente dello schema provvisorio; validazione hardware pendente
SW1,MX2A-11NW,1,Button_Switch_Keyboard:SW_Cherry_MX_1.00u_PCB,MX2A-11NW,CHERRY,https://www.mouser.com/PCN/CHERRY_MX1A_11NW_EOL.pdf,,yes,Componente dello schema provvisorio; validazione hardware pendente
SW2,MX2A-11NW,1,Button_Switch_Keyboard:SW_Cherry_MX_1.00u_PCB,MX2A-11NW,CHERRY,https://www.mouser.com/PCN/CHERRY_MX1A_11NW_EOL.pdf,,yes,Componente dello schema provvisorio; validazione hardware pendente
SW3,MX2A-11NW,1,Button_Switch_Keyboard:SW_Cherry_MX_1.00u_PCB,MX2A-11NW,CHERRY,https://www.mouser.com/PCN/CHERRY_MX1A_11NW_EOL.pdf,,yes,Componente dello schema provvisorio; validazione hardware pendente
SW4,MX2A-11NW,1,Button_Switch_Keyboard:SW_Cherry_MX_1.00u_PCB,MX2A-11NW,CHERRY,https://www.mouser.com/PCN/CHERRY_MX1A_11NW_EOL.pdf,,yes,Componente dello schema provvisorio; validazione hardware pendente
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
